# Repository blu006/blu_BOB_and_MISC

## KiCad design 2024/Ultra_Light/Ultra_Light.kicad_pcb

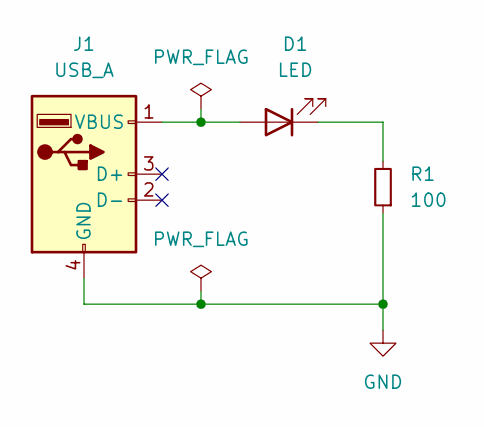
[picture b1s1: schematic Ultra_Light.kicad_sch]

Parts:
D1: LED; LED_D5.0mm
J1: USB_A; usb-PCB-holes
R1: 100; R_0805_2012Metric_Pad1.20x1.40mm_HandSolder

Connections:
GND: J1.4 (GND), R1.1
unnamed: D1.2 (A), J1.1 (VBUS)
unnamed: D1.1 (K), R1.2

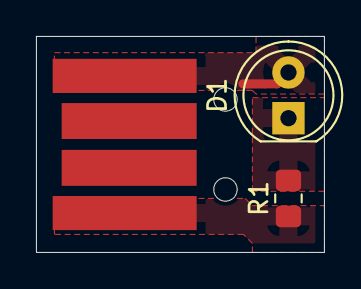
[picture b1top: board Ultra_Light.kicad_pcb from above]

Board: 2 copper layers, 16.0 x 12.0 mm, 3 parts (0 on the bottom side), 3 nets.

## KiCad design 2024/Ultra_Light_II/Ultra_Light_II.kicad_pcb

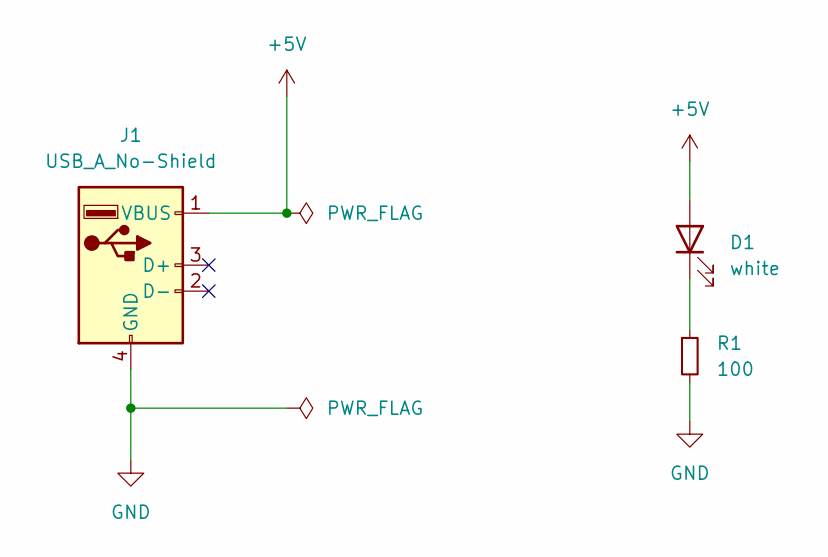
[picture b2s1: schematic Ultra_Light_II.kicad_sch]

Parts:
D1: white; LED_D5.0mm
J1: USB_A_No-Shield; usb-PCB-holes
R1: 100; R_0402_1005Metric

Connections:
+5V: D1.2 (A), J1.1 (VBUS)
GND: J1.4 (GND), R1.2
unnamed: D1.1 (K), R1.1

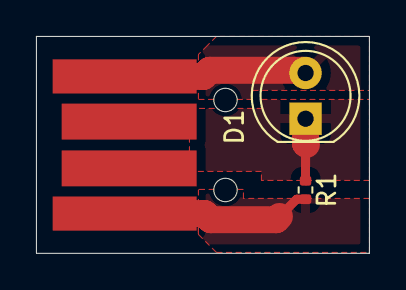
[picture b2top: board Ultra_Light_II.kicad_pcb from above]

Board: 2 copper layers, 18.5 x 12.0 mm, 3 parts (0 on the bottom side), 3 nets.

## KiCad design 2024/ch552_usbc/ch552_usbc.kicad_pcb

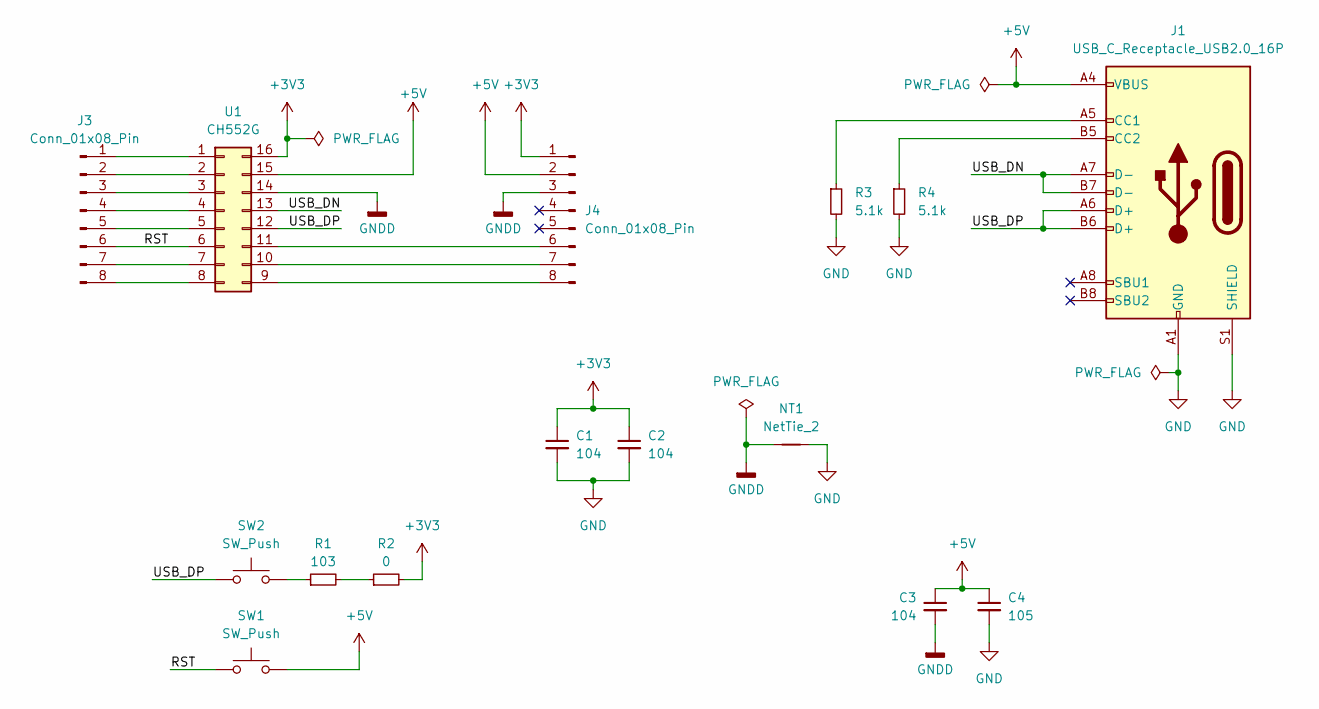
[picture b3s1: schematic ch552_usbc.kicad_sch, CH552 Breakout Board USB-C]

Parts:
C1, C2, C3: 104; C_0603_1608Metric
C4: 105; C_0805_2012Metric
J1: USB_C_Receptacle_USB2.0_16P; USB_C_Receptacle_XKB_U262-16XN-4BVC11
J3, J4: Conn_01x08_Pin; PinHeader_1x08_P2.54mm_Vertical
NT1: NetTie_2; R_0603_1608Metric
R1: 103; R_0603_1608Metric
R2: 0; R_0603_1608Metric
R3, R4: 5.1k; R_0603_1608Metric
SW1, SW2: SW_Push; SW_PUSH_6mm
U1: CH552G; SOIC-16_3.9x9.9mm_P1.27mm

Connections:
+3V3: C1.1, C2.1, J4.1, R2.2, U1.16
+5V: C3.1, C4.1, J1.A4 (VBUS), J1.A9 (VBUS), J1.B4 (VBUS), J1.B9 (VBUS), J4.2, SW1.2, U1.15
/RST: J3.6, SW1.1, U1.6
/USB_DN: J1.A7 (D-), J1.B7 (D-), U1.13
/USB_DP: J1.A6 (D+), J1.B6 (D+), SW2.1, U1.12
GND: C1.2, C2.2, C4.2, J1.A1 (GND), J1.A12 (GND), J1.B1 (GND), J1.B12 (GND), J1.S1 (SHIELD), NT1.2, R3.2, R4.2
GNDD: C3.2, J4.3, NT1.1, U1.14
unnamed: J1.A5 (CC1), R3.1
unnamed: J1.B5 (CC2), R4.1
unnamed: J3.1, U1.1
unnamed: J3.2, U1.2
unnamed: J3.3, U1.3
unnamed: J3.4, U1.4
unnamed: J3.5, U1.5
unnamed: J3.7, U1.7
unnamed: J3.8, U1.8
unnamed: J4.6, U1.11
unnamed: J4.7, U1.10
unnamed: J4.8, U1.9
unnamed: R1.1, SW2.2
unnamed: R1.2, R2.1

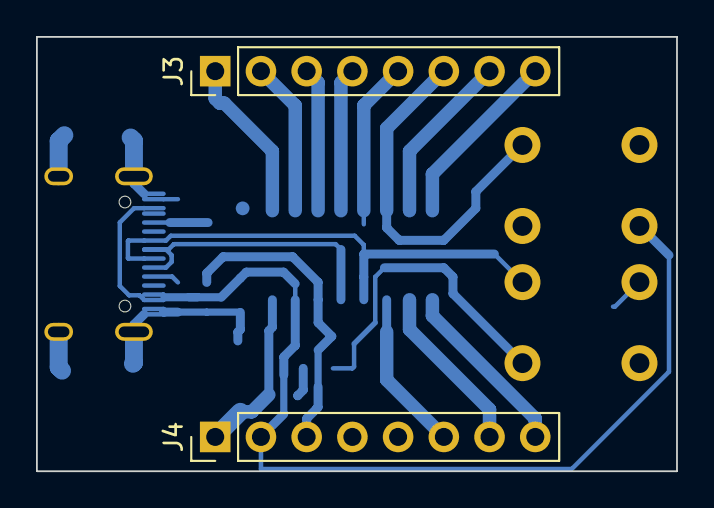
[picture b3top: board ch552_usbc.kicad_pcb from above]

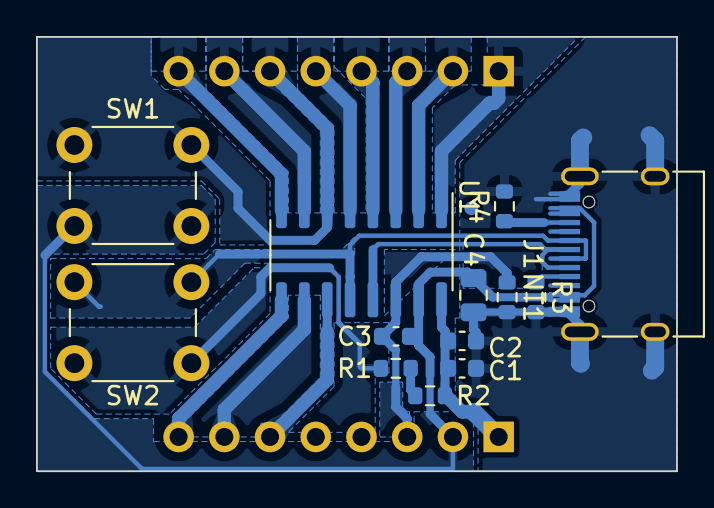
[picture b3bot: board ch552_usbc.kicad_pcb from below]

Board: 2 copper layers, 35.6 x 24.1 mm, 15 parts (13 on the bottom side), 21 nets.

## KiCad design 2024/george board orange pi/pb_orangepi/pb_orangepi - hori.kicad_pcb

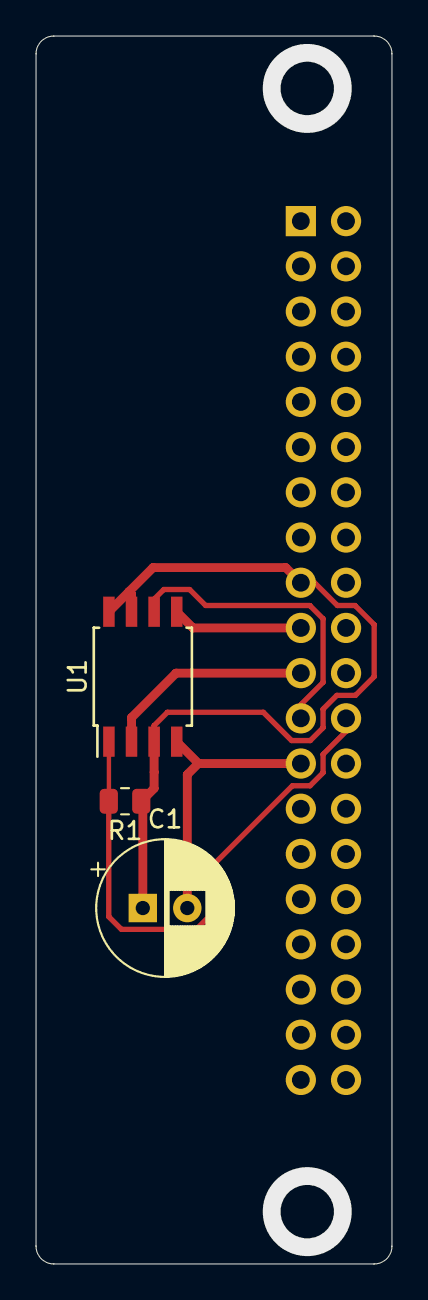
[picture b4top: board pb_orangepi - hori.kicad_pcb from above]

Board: 2 copper layers, 20.0 x 69.0 mm, 4 parts (1 on the bottom side), 6 nets.

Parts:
C1: 47uF; CP_Radial_D7.5mm_P2.50mm
J1: Conn_02x20_Odd_Even; PinSocket_2x20_P2.54mm_Vertical
R1: 10k; R_0805_2012Metric
U1: S25FL216K; SOIC-8W_5.3x5.3mm_P1.27mm

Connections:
+3V3: C1.1, J1.17, R1.1, U1.3 (W#/VPP), U1.7 (HOLD#), U1.8 (VCC)
/SPI0_CLK: J1.23, U1.6 (C)
/SPI0_CS0: J1.24, R1.2, U1.1 (S#)
/SPI0_MISO: J1.21, U1.2 (DQ1)
/SPI0_MOSI: J1.19, U1.5 (DQ0)
GND: C1.2, J1.25, U1.4 (VSS)

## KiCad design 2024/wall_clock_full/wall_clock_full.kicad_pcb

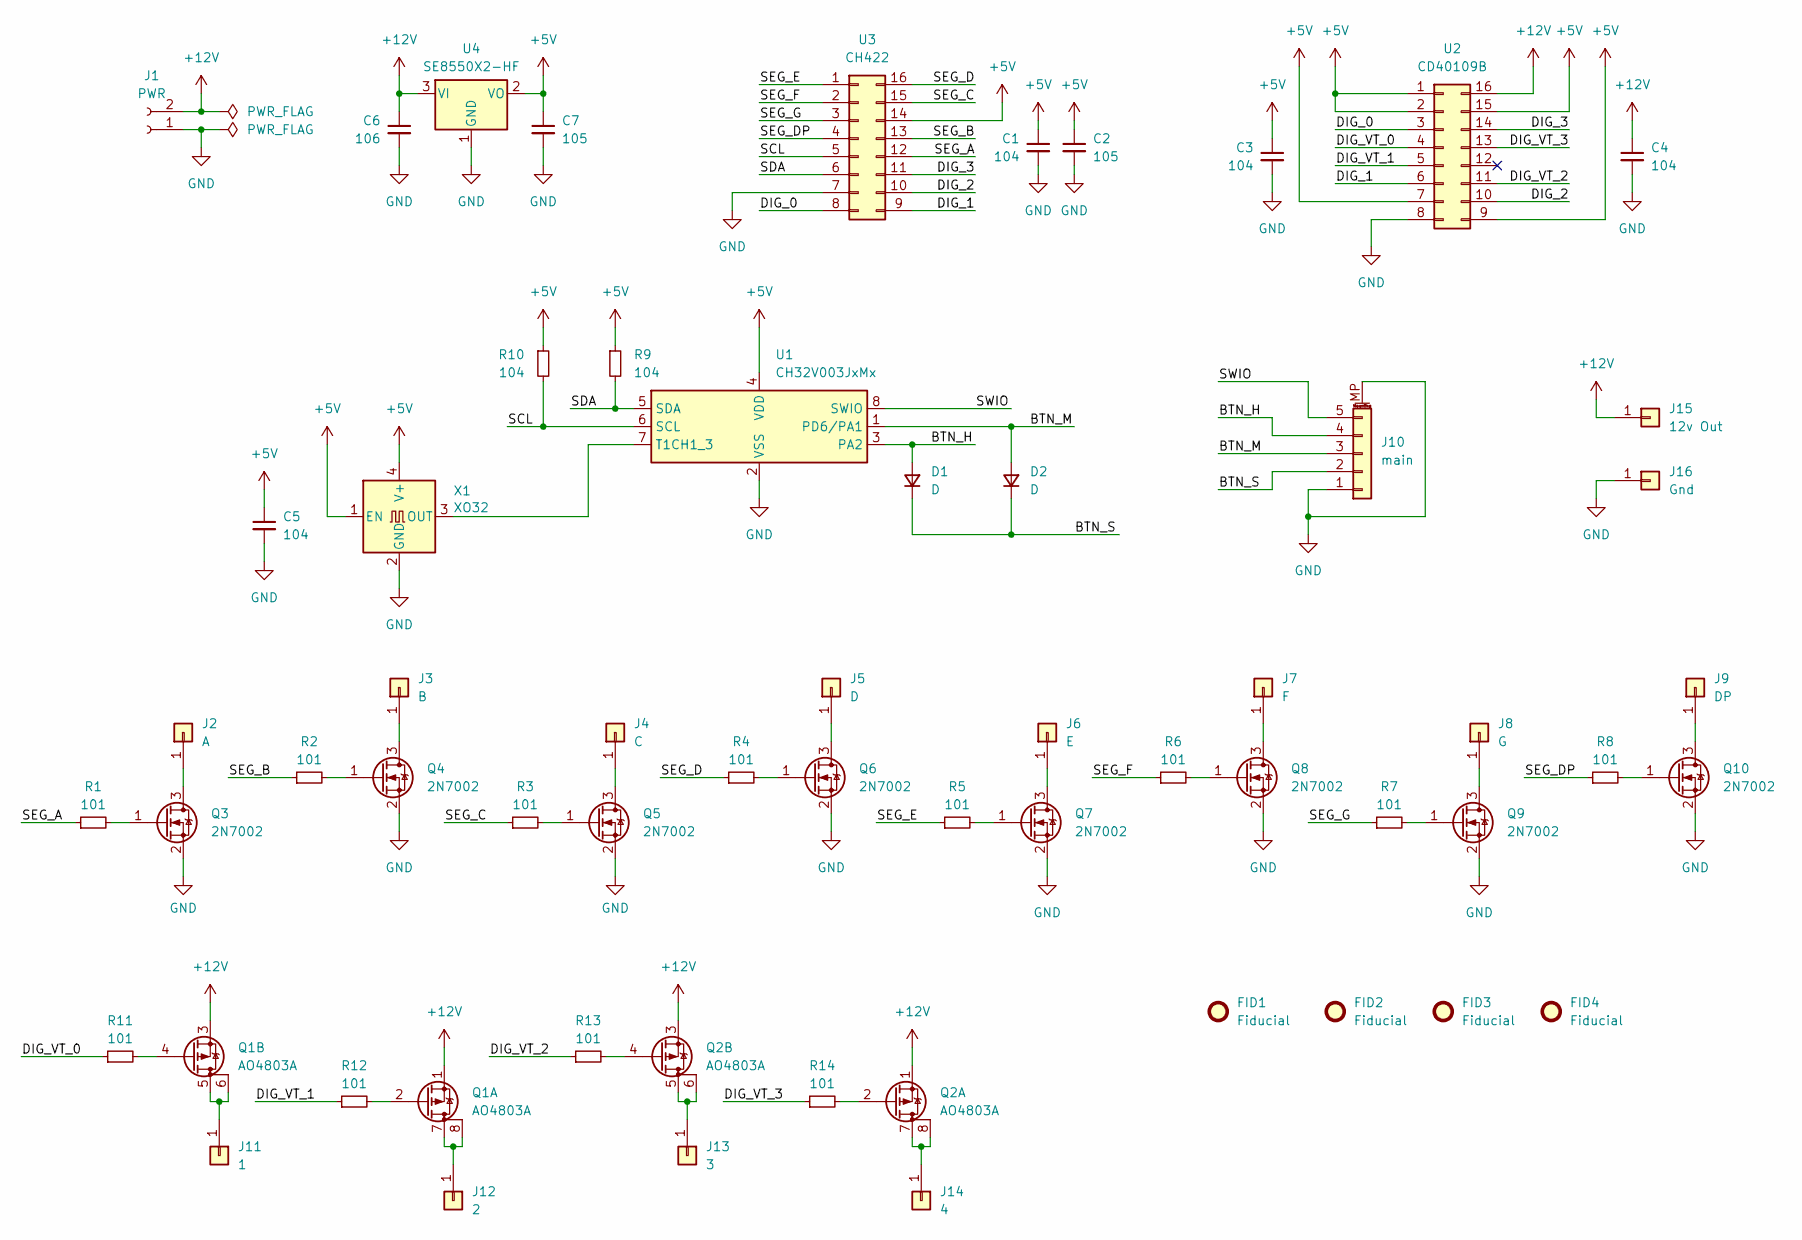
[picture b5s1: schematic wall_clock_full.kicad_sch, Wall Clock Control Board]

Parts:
C1, C3, C4, C5: 104; C_0603_1608Metric
C2, C7: 105; C_0805_2012Metric
C6: 106; C_1206_3216Metric
D1, D2: D; D_DO-35_SOD27_P7.62mm_Horizontal
FID1, FID2, FID3, FID4: Fiducial; Fiducial_0.5mm_Mask1.5mm
J1: PWR; TerminalBlock_bornier-2_P5.08mm
J2: A; Conn_PCB_Castellated_1x01_P2.54mm_ExtraHole
J3: B; Conn_PCB_Castellated_1x01_P2.54mm_ExtraHole
J4: C; Conn_PCB_Castellated_1x01_P2.54mm_ExtraHole
J5: D; Conn_PCB_Castellated_1x01_P2.54mm_ExtraHole
J6: E; Conn_PCB_Castellated_1x01_P2.54mm_ExtraHole
J7: F; Conn_PCB_Castellated_1x01_P2.54mm_ExtraHole
J8: G; Conn_PCB_Castellated_1x01_P2.54mm_ExtraHole
J9: DP; Conn_PCB_Castellated_1x01_P2.54mm_ExtraHole
J10: main; JST_PH_S5B-PH-SM4-TB_1x05-1MP_P2.00mm_Horizontal
J11: 1; Conn_PCB_Castellated_1x01_P2.54mm_ExtraHole
J12: 2; Conn_PCB_Castellated_1x01_P2.54mm_ExtraHole
J13: 3; Conn_PCB_Castellated_1x01_P2.54mm_ExtraHole
J14: 4; Conn_PCB_Castellated_1x01_P2.54mm_ExtraHole
J15: 12v Out; Conn_PCB_Castellated_1x01_P2.54mm_ExtraHole
J16: Gnd; Conn_PCB_Castellated_1x01_P2.54mm_ExtraHole
Q1, Q2: AO4803A; SOIC-8_3.9x4.9mm_P1.27mm
Q3, Q4, Q5, Q6, Q7, Q8, Q9, Q10: 2N7002; SOT-23
R1, R2, R3, R4, R5, R6, R7, R8, R11, R12, R13, R14: 101; R_0402_1005Metric
R9, R10: 104; R_0603_1608Metric
U1: CH32V003JxMx; SOP-8_3.9x4.9mm_P1.27mm
U2: CD40109B; SO-16_5.3x10.2mm_P1.27mm
U3: CH422; SO-16_3.9x9.9mm_P1.27mm
U4: SE8550X2-HF; SOT-23
X1: XO32; Oscillator_SMD_EuroQuartz_XO32-4Pin_3.2x2.5mm

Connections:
+5V: C1.1, C2.1, C3.1, C5.1, C7.1, R9.1, R10.1, U1.4 (VDD), U2.1, U2.2, U2.7, U2.9, U2.15, U3.14, U4.2 (VO), X1.1 (EN), X1.4 (V+)
+12V: C4.1, C6.1, J1.2, J15.1, Q1.1 (S), Q1.3 (S), Q2.1 (S), Q2.3 (S), U2.16, U4.3 (VI)
/BTN_H: D1.2 (A), J10.4, U1.3 (PA2)
/BTN_M: D2.2 (A), J10.3, U1.1 (PD6/PA1)
/BTN_S: D1.1 (K), D2.1 (K), J10.2
/DIG_0: U2.3, U3.8
/DIG_1: U2.6, U3.9
/DIG_2: U2.10, U3.10
/DIG_3: U2.14, U3.11
/DIG_VT_0: R11.1, U2.4
/DIG_VT_1: R12.1, U2.5
/DIG_VT_2: R13.1, U2.11
/DIG_VT_3: R14.1, U2.13
/SCL: R10.2, U1.6 (SCL), U3.5
/SDA: R9.2, U1.5 (SDA), U3.6
/SEG_A: R1.1, U3.12
/SEG_B: R2.1, U3.13
/SEG_C: R3.1, U3.15
/SEG_D: R4.1, U3.16
/SEG_DP: R8.1, U3.4
/SEG_E: R5.1, U3.1
/SEG_F: R6.1, U3.2
/SEG_G: R7.1, U3.3
/SWIO: J10.5, U1.8 (SWIO)
GND: C1.2, C2.2, C3.2, C4.2, C5.2, C6.2, C7.2, J1.1, J10.1, J10.MP (MountPin), J16.1, Q3.2 (S), Q4.2 (S), Q5.2 (S), Q6.2 (S), Q7.2 (S), Q8.2 (S), Q9.2 (S), Q10.2 (S), U1.2 (VSS), U2.8, U3.7, U4.1 (GND), X1.2 (GND)
unnamed: J2.1, Q3.3 (D)
unnamed: J3.1, Q4.3 (D)
unnamed: J4.1, Q5.3 (D)
unnamed: J5.1, Q6.3 (D)
unnamed: J6.1, Q7.3 (D)
unnamed: J7.1, Q8.3 (D)
unnamed: J8.1, Q9.3 (D)
unnamed: J9.1, Q10.3 (D)
unnamed: J11.1, Q1.5 (D), Q1.6 (G)
unnamed: J12.1, Q1.7 (D), Q1.8 (G)
unnamed: J13.1, Q2.5 (D), Q2.6 (G)
unnamed: J14.1, Q2.7 (D), Q2.8 (G)
unnamed: Q1.2 (G), R12.2
unnamed: Q1.4 (G), R11.2
unnamed: Q2.2 (G), R14.2
unnamed: Q2.4 (G), R13.2
unnamed: Q3.1 (G), R1.2
unnamed: Q4.1 (G), R2.2
unnamed: Q5.1 (G), R3.2
unnamed: Q6.1 (G), R4.2
unnamed: Q7.1 (G), R5.2
unnamed: Q8.1 (G), R6.2
unnamed: Q9.1 (G), R7.2
unnamed: Q10.1 (G), R8.2
unnamed: U1.7 (T1CH1_3), X1.3 (OUT)

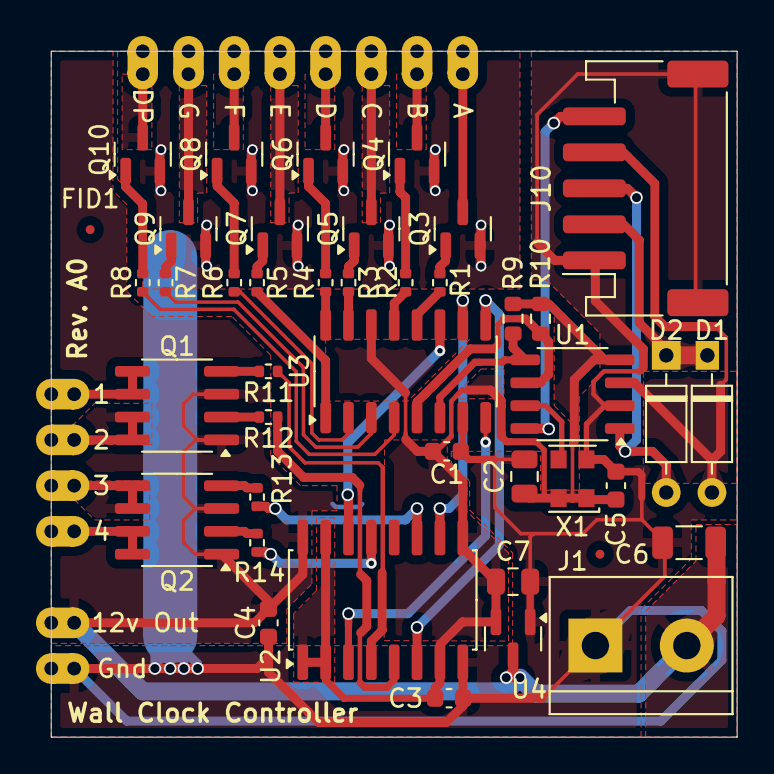
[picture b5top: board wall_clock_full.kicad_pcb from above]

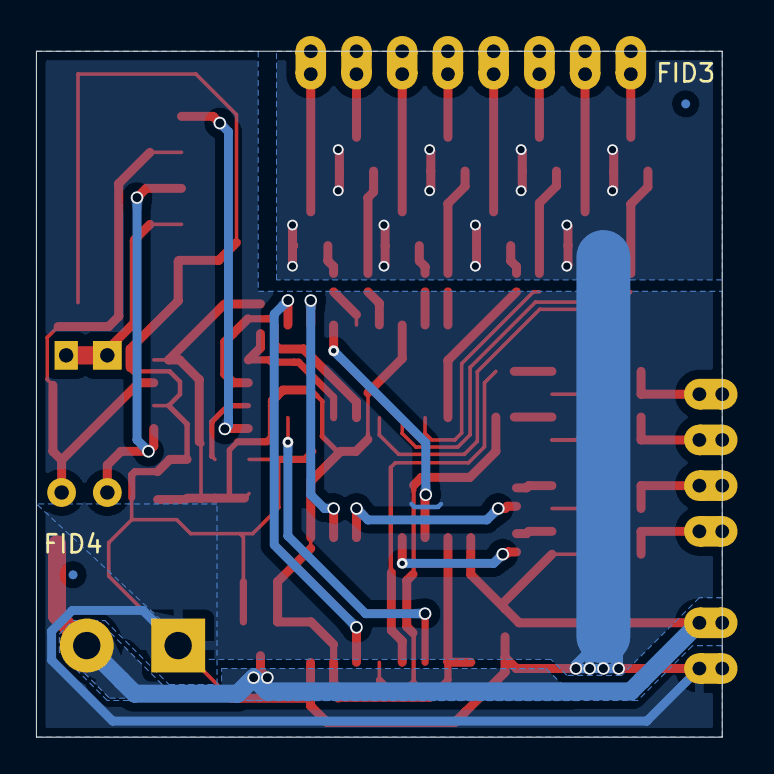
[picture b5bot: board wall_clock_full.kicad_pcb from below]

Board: 2 copper layers, 38.1 x 38.1 mm, 58 parts (2 on the bottom side), 50 nets.
